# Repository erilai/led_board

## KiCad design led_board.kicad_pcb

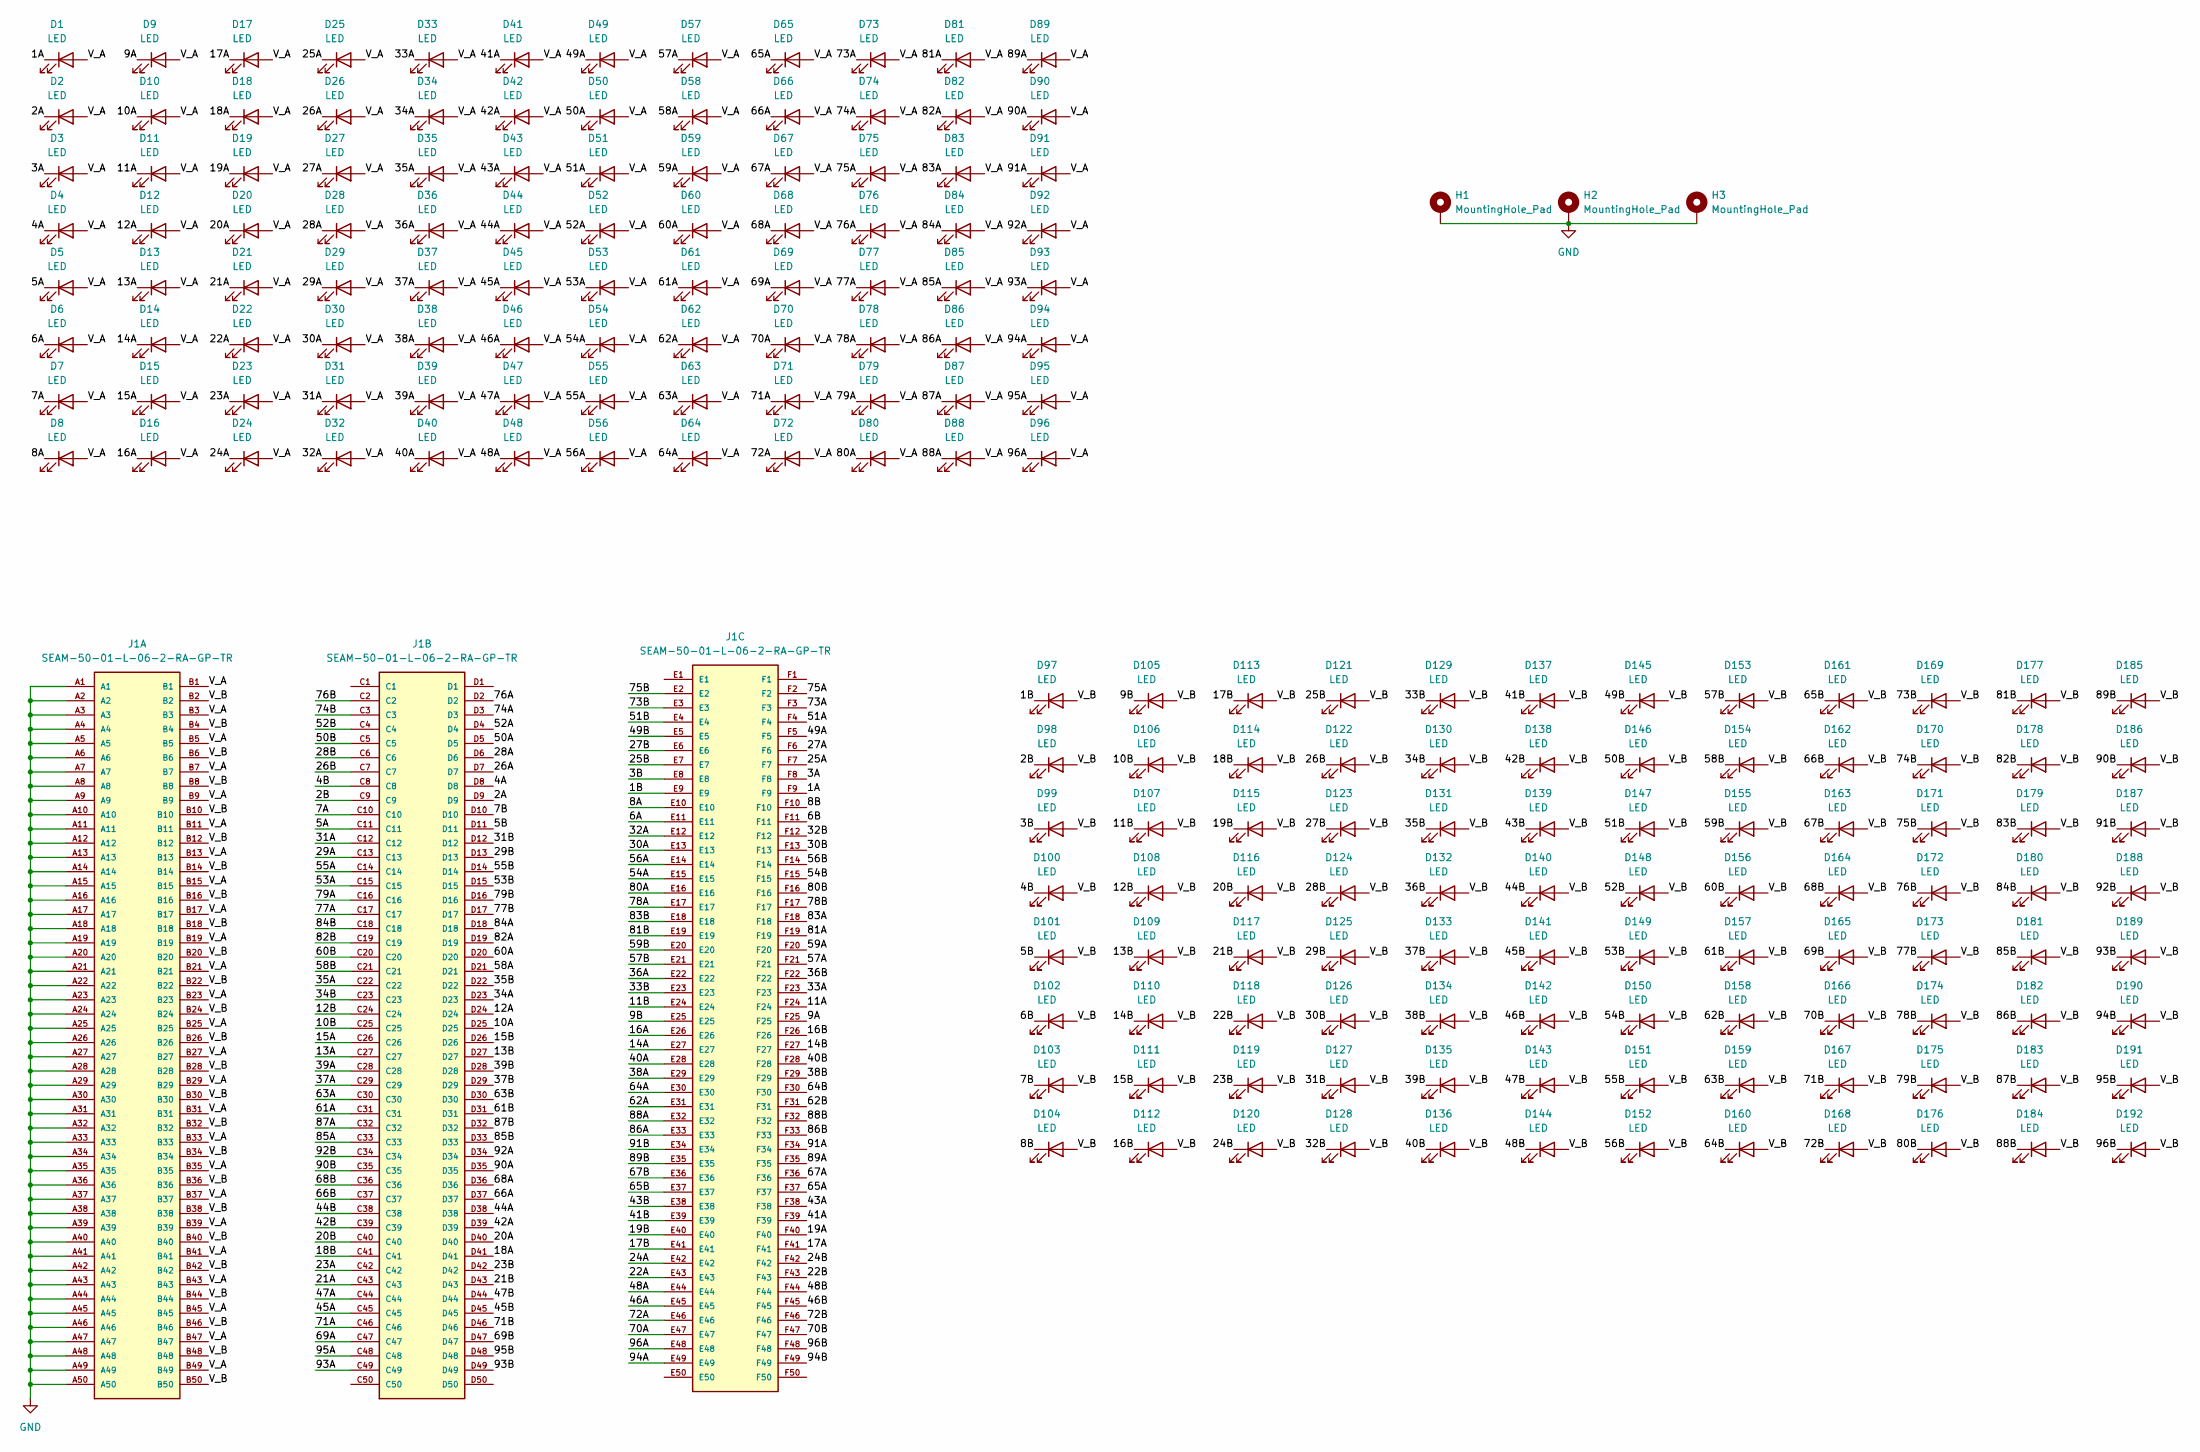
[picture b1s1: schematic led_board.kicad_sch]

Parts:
D1, D2, D3, D4, D5, D6, D7, D8, D9, D10, D11, D12, D13, D14, D15, D16, D17, D18, D19, D20, D21, D22, D23, D24, D25, D26, D27, D28, D29, D30, D31, D32, D33, D34, D35, D36, D37, D38, D39, D40, D41, D42, D43, D44, D45, D46, D47, D48, D49, D50, D51, D52, D53, D54, D55, D56, D57, D58, D59, D60, D61, D62, D63, D64, D65, D66, D67, D68, D69, D70, D71, D72, D73, D74, D75, D76, D77, D78, D79, D80, D81, D82, D83, D84, D85, D86, D87, D88, D89, D90, D91, D92, D93, D94, D95, D96: LED; SMTL3528UV-405
D97, D98, D99, D100, D101, D102, D103, D104, D105, D106, D107, D108, D109, D110, D111, D112, D113, D114, D115, D116, D117, D118, D119, D120, D121, D122, D123, D124, D125, D126, D127, D128, D129, D130, D131, D132, D133, D134, D135, D136, D137, D138, D139, D140, D141, D142, D143, D144, D145, D146, D147, D148, D149, D150, D151, D152, D153, D154, D155, D156, D157, D158, D159, D160, D161, D162, D163, D164, D165, D166, D167, D168, D169, D170, D171, D172, D173, D174, D175, D176, D177, D178, D179, D180, D181, D182, D183, D184, D185, D186, D187, D188, D189, D190, D191, D192: LED; GFJTLPS124KXK511
H1, H2, H3: MountingHole_Pad; MountingHole_3.5mm_Pad_TopBottom
J1: SEAM-50-01-L-06-2-RA-GP-TR; SAMTEC_SEAM-50-01-L-06-2-RA-GP-TR; PARTREV R

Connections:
/1A: D1.1 (K), J1.F9
/1B: D97.1 (K), J1.E9
/2A: D2.1 (K), J1.D9
/2B: D98.1 (K), J1.C9
/3A: D3.1 (K), J1.F8
/3B: D99.1 (K), J1.E8
/4A: D4.1 (K), J1.D8
/4B: D100.1 (K), J1.C8
/5A: D5.1 (K), J1.C11
/5B: D101.1 (K), J1.D11
/6A: D6.1 (K), J1.E11
/6B: D102.1 (K), J1.F11
/7A: D7.1 (K), J1.C10
/7B: D103.1 (K), J1.D10
/8A: D8.1 (K), J1.E10
/8B: D104.1 (K), J1.F10
/9A: D9.1 (K), J1.F25
/9B: D105.1 (K), J1.E25
/10A: D10.1 (K), J1.D25
/10B: D106.1 (K), J1.C25
/11A: D11.1 (K), J1.F24
/11B: D107.1 (K), J1.E24
/12A: D12.1 (K), J1.D24
/12B: D108.1 (K), J1.C24
/13A: D13.1 (K), J1.C27
/13B: D109.1 (K), J1.D27
/14A: D14.1 (K), J1.E27
/14B: D110.1 (K), J1.F27
/15A: D15.1 (K), J1.C26
/15B: D111.1 (K), J1.D26
/16A: D16.1 (K), J1.E26
/16B: D112.1 (K), J1.F26
/17A: D17.1 (K), J1.F41
/17B: D113.1 (K), J1.E41
/18A: D18.1 (K), J1.D41
/18B: D114.1 (K), J1.C41
/19A: D19.1 (K), J1.F40
/19B: D115.1 (K), J1.E40
/20A: D20.1 (K), J1.D40
/20B: D116.1 (K), J1.C40
/21A: D21.1 (K), J1.C43
/21B: D117.1 (K), J1.D43
/22A: D22.1 (K), J1.E43
/22B: D118.1 (K), J1.F43
/23A: D23.1 (K), J1.C42
/23B: D119.1 (K), J1.D42
/24A: D24.1 (K), J1.E42
/24B: D120.1 (K), J1.F42
/25A: D25.1 (K), J1.F7
/25B: D121.1 (K), J1.E7
/26A: D26.1 (K), J1.D7
/26B: D122.1 (K), J1.C7
/27A: D27.1 (K), J1.F6
/27B: D123.1 (K), J1.E6
/28A: D28.1 (K), J1.D6
/28B: D124.1 (K), J1.C6
/29A: D29.1 (K), J1.C13
/29B: D125.1 (K), J1.D13
/30A: D30.1 (K), J1.E13
/30B: D126.1 (K), J1.F13
/31A: D31.1 (K), J1.C12
/31B: D127.1 (K), J1.D12
/32A: D32.1 (K), J1.E12
/32B: D128.1 (K), J1.F12
/33A: D33.1 (K), J1.F23
/33B: D129.1 (K), J1.E23
/34A: D34.1 (K), J1.D23
/34B: D130.1 (K), J1.C23
/35A: D35.1 (K), J1.C22
/35B: D131.1 (K), J1.D22
/36A: D36.1 (K), J1.E22
/36B: D132.1 (K), J1.F22
/37A: D37.1 (K), J1.C29
/37B: D133.1 (K), J1.D29
/38A: D38.1 (K), J1.E29
/38B: D134.1 (K), J1.F29
/39A: D39.1 (K), J1.C28
/39B: D135.1 (K), J1.D28
/40A: D40.1 (K), J1.E28
/40B: D136.1 (K), J1.F28
/41A: D41.1 (K), J1.F39
/41B: D137.1 (K), J1.E39
/42A: D42.1 (K), J1.D39
/42B: D138.1 (K), J1.C39
/43A: D43.1 (K), J1.F38
/43B: D139.1 (K), J1.E38
/44A: D44.1 (K), J1.D38
/44B: D140.1 (K), J1.C38
/45A: D45.1 (K), J1.C45
/45B: D141.1 (K), J1.D45
/46A: D46.1 (K), J1.E45
/46B: D142.1 (K), J1.F45
/47A: D47.1 (K), J1.C44
/47B: D143.1 (K), J1.D44
/48A: D48.1 (K), J1.E44
/48B: D144.1 (K), J1.F44
/49A: D49.1 (K), J1.F5
/49B: D145.1 (K), J1.E5
/50A: D50.1 (K), J1.D5
/50B: D146.1 (K), J1.C5
/51A: D51.1 (K), J1.F4
/51B: D147.1 (K), J1.E4
/52A: D52.1 (K), J1.D4
/52B: D148.1 (K), J1.C4
/53A: D53.1 (K), J1.C15
/53B: D149.1 (K), J1.D15
/54A: D54.1 (K), J1.E15
/54B: D150.1 (K), J1.F15
/55A: D55.1 (K), J1.C14
/55B: D151.1 (K), J1.D14
/56A: D56.1 (K), J1.E14
/56B: D152.1 (K), J1.F14
/57A: D57.1 (K), J1.F21
/57B: D153.1 (K), J1.E21
/58A: D58.1 (K), J1.D21
/58B: D154.1 (K), J1.C21
/59A: D59.1 (K), J1.F20
/59B: D155.1 (K), J1.E20
/60A: D60.1 (K), J1.D20
/60B: D156.1 (K), J1.C20
/61A: D61.1 (K), J1.C31
/61B: D157.1 (K), J1.D31
/62A: D62.1 (K), J1.E31
/62B: D158.1 (K), J1.F31
/63A: D63.1 (K), J1.C30
/63B: D159.1 (K), J1.D30
/64A: D64.1 (K), J1.E30
/64B: D160.1 (K), J1.F30
/65A: D65.1 (K), J1.F37
/65B: D161.1 (K), J1.E37
/66A: D66.1 (K), J1.D37
/66B: D162.1 (K), J1.C37
/67A: D67.1 (K), J1.F36
/67B: D163.1 (K), J1.E36
/68A: D68.1 (K), J1.D36
/68B: D164.1 (K), J1.C36
/69A: D69.1 (K), J1.C47
/69B: D165.1 (K), J1.D47
/70A: D70.1 (K), J1.E47
/70B: D166.1 (K), J1.F47
/71A: D71.1 (K), J1.C46
/71B: D167.1 (K), J1.D46
/72A: D72.1 (K), J1.E46
/72B: D168.1 (K), J1.F46
/73A: D73.1 (K), J1.F3
/73B: D169.1 (K), J1.E3
/74A: D74.1 (K), J1.D3
/74B: D170.1 (K), J1.C3
/75A: D75.1 (K), J1.F2
/75B: D171.1 (K), J1.E2
/76A: D76.1 (K), J1.D2
/76B: D172.1 (K), J1.C2
/77A: D77.1 (K), J1.C17
/77B: D173.1 (K), J1.D17
/78A: D78.1 (K), J1.E17
/78B: D174.1 (K), J1.F17
/79A: D79.1 (K), J1.C16
/79B: D175.1 (K), J1.D16
/80A: D80.1 (K), J1.E16
/80B: D176.1 (K), J1.F16
/81A: D81.1 (K), J1.F19
/81B: D177.1 (K), J1.E19
/82A: D82.1 (K), J1.D19
/82B: D178.1 (K), J1.C19
/83A: D83.1 (K), J1.F18
/83B: D179.1 (K), J1.E18
/84A: D84.1 (K), J1.D18
/84B: D180.1 (K), J1.C18
/85A: D85.1 (K), J1.C33
/85B: D181.1 (K), J1.D33
/86A: D86.1 (K), J1.E33
/86B: D182.1 (K), J1.F33
/87A: D87.1 (K), J1.C32
/87B: D183.1 (K), J1.D32
/88A: D88.1 (K), J1.E32
/88B: D184.1 (K), J1.F32
/89A: D89.1 (K), J1.F35
/89B: D185.1 (K), J1.E35
/90A: D90.1 (K), J1.D35
/90B: D186.1 (K), J1.C35
/91A: D91.1 (K), J1.F34
/91B: D187.1 (K), J1.E34
/92A: D92.1 (K), J1.D34
/92B: D188.1 (K), J1.C34
/93A: D93.1 (K), J1.C49
/93B: D189.1 (K), J1.D49
/94A: D94.1 (K), J1.E49
/94B: D190.1 (K), J1.F49
/95A: D95.1 (K), J1.C48
/95B: D191.1 (K), J1.D48
/96A: D96.1 (K), J1.E48
/96B: D192.1 (K), J1.F48
/V_A: D1.2 (A), D2.2 (A), D3.2 (A), D4.2 (A), D5.2 (A), D6.2 (A), D7.2 (A), D8.2 (A), D9.2 (A), D10.2 (A), D11.2 (A), D12.2 (A), D13.2 (A), D14.2 (A), D15.2 (A), D16.2 (A), D17.2 (A), D18.2 (A), D19.2 (A), D20.2 (A), D21.2 (A), D22.2 (A), D23.2 (A), D24.2 (A), D25.2 (A), D26.2 (A), D27.2 (A), D28.2 (A), D29.2 (A), D30.2 (A), D31.2 (A), D32.2 (A), D33.2 (A), D34.2 (A), D35.2 (A), D36.2 (A), D37.2 (A), D38.2 (A), D39.2 (A), D40.2 (A), D41.2 (A), D42.2 (A), D43.2 (A), D44.2 (A), D45.2 (A), D46.2 (A), D47.2 (A), D48.2 (A), D49.2 (A), D50.2 (A), D51.2 (A), D52.2 (A), D53.2 (A), D54.2 (A), D55.2 (A), D56.2 (A), D57.2 (A), D58.2 (A), D59.2 (A), D60.2 (A), D61.2 (A), D62.2 (A), D63.2 (A), D64.2 (A), D65.2 (A), D66.2 (A), D67.2 (A), D68.2 (A), D69.2 (A), D70.2 (A), D71.2 (A), D72.2 (A), D73.2 (A), D74.2 (A), D75.2 (A), D76.2 (A), D77.2 (A), D78.2 (A), D79.2 (A), D80.2 (A), D81.2 (A), D82.2 (A), D83.2 (A), D84.2 (A), D85.2 (A), D86.2 (A), D87.2 (A), D88.2 (A), D89.2 (A), D90.2 (A), D91.2 (A), D92.2 (A), D93.2 (A), D94.2 (A), D95.2 (A), D96.2 (A), J1.B1, J1.B3, J1.B5, J1.B7, J1.B9, J1.B11, J1.B13, J1.B15, J1.B17, J1.B19, J1.B21, J1.B23, J1.B25, J1.B27, J1.B29, J1.B31, J1.B33, J1.B35, J1.B37, J1.B39, J1.B41, J1.B43, J1.B45, J1.B47, J1.B49
/V_B: D97.2 (A), D98.2 (A), D99.2 (A), D100.2 (A), D101.2 (A), D102.2 (A), D103.2 (A), D104.2 (A), D105.2 (A), D106.2 (A), D107.2 (A), D108.2 (A), D109.2 (A), D110.2 (A), D111.2 (A), D112.2 (A), D113.2 (A), D114.2 (A), D115.2 (A), D116.2 (A), D117.2 (A), D118.2 (A), D119.2 (A), D120.2 (A), D121.2 (A), D122.2 (A), D123.2 (A), D124.2 (A), D125.2 (A), D126.2 (A), D127.2 (A), D128.2 (A), D129.2 (A), D130.2 (A), D131.2 (A), D132.2 (A), D133.2 (A), D134.2 (A), D135.2 (A), D136.2 (A), D137.2 (A), D138.2 (A), D139.2 (A), D140.2 (A), D141.2 (A), D142.2 (A), D143.2 (A), D144.2 (A), D145.2 (A), D146.2 (A), D147.2 (A), D148.2 (A), D149.2 (A), D150.2 (A), D151.2 (A), D152.2 (A), D153.2 (A), D154.2 (A), D155.2 (A), D156.2 (A), D157.2 (A), D158.2 (A), D159.2 (A), D160.2 (A), D161.2 (A), D162.2 (A), D163.2 (A), D164.2 (A), D165.2 (A), D166.2 (A), D167.2 (A), D168.2 (A), D169.2 (A), D170.2 (A), D171.2 (A), D172.2 (A), D173.2 (A), D174.2 (A), D175.2 (A), D176.2 (A), D177.2 (A), D178.2 (A), D179.2 (A), D180.2 (A), D181.2 (A), D182.2 (A), D183.2 (A), D184.2 (A), D185.2 (A), D186.2 (A), D187.2 (A), D188.2 (A), D189.2 (A), D190.2 (A), D191.2 (A), D192.2 (A), J1.B2, J1.B4, J1.B6, J1.B8, J1.B10, J1.B12, J1.B14, J1.B16, J1.B18, J1.B20, J1.B22, J1.B24, J1.B26, J1.B28, J1.B30, J1.B32, J1.B34, J1.B36, J1.B38, J1.B40, J1.B42, J1.B44, J1.B46, J1.B48, J1.B50
GND: H1.1, H2.1, H3.1, J1.A1, J1.A2, J1.A3, J1.A4, J1.A5, J1.A6, J1.A7, J1.A8, J1.A9, J1.A10, J1.A11, J1.A12, J1.A13, J1.A14, J1.A15, J1.A16, J1.A17, J1.A18, J1.A19, J1.A20, J1.A21, J1.A22, J1.A23, J1.A24, J1.A25, J1.A26, J1.A27, J1.A28, J1.A29, J1.A30, J1.A31, J1.A32, J1.A33, J1.A34, J1.A35, J1.A36, J1.A37, J1.A38, J1.A39, J1.A40, J1.A41, J1.A42, J1.A43, J1.A44, J1.A45, J1.A46, J1.A47, J1.A48, J1.A49, J1.A50; also elsewhere on the board

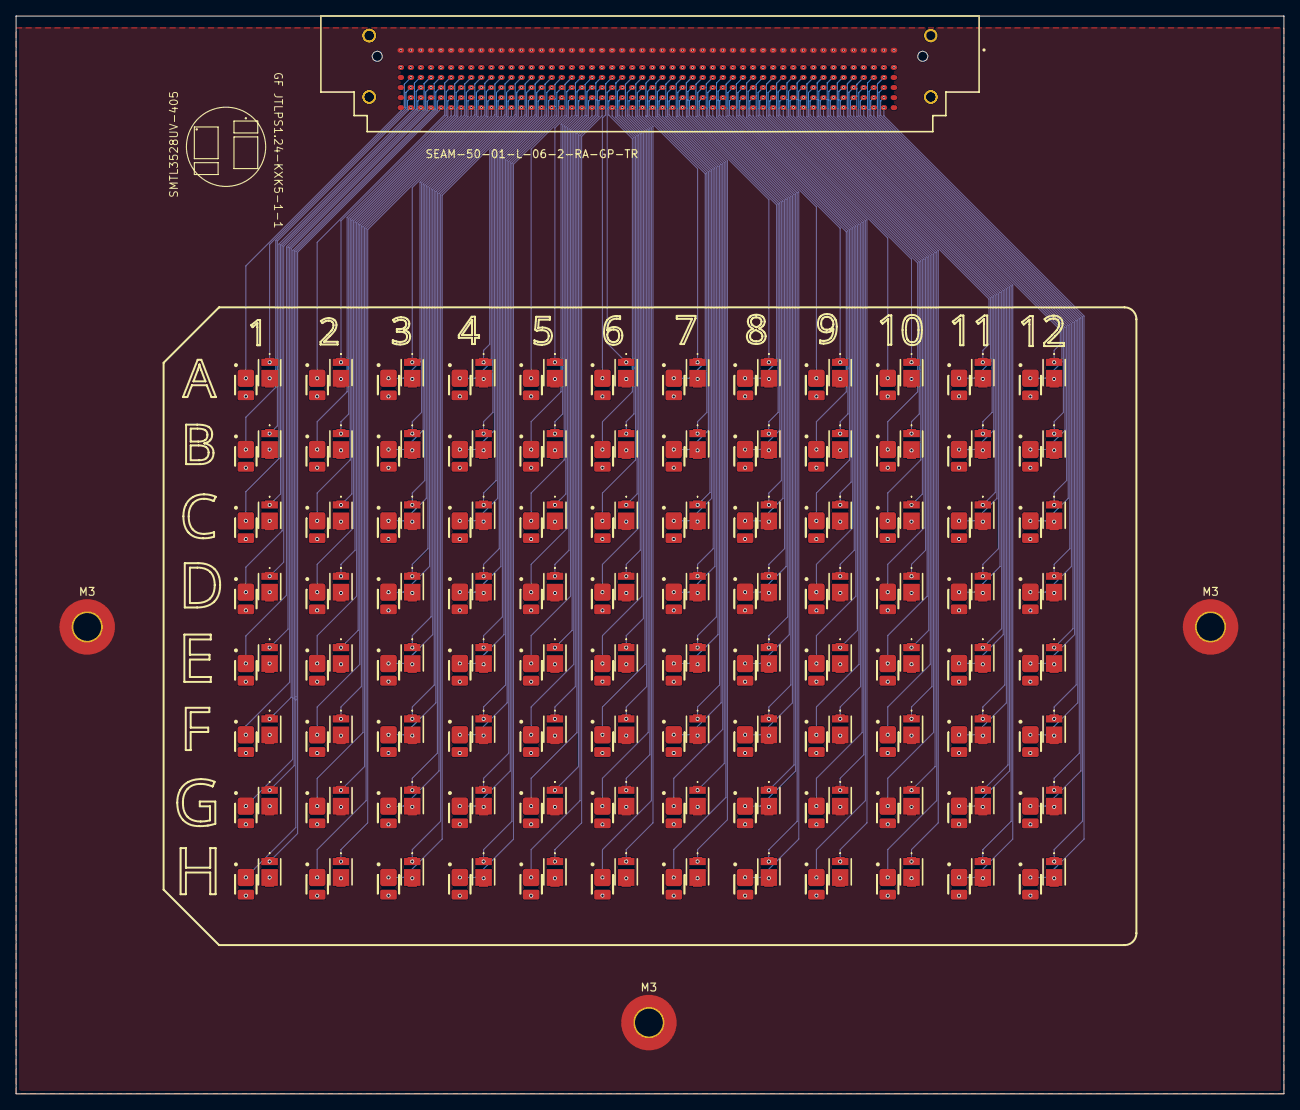
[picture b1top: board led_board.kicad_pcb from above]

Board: 4 copper layers, 160.0 x 136.0 mm, 196 parts (0 on the bottom side), 195 nets.

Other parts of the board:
M3, M3#2, M3#3: MountingHole_Pad; MountingHole_3.5mm_Pad_TopBottom

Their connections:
GND: M3.1 (1_1), M3#2.1 (1_1), M3#3.1 (1_1); also elsewhere on the board
